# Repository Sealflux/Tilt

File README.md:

## Tilt
-- I put photo here once I have!

## Description
A motion-controlled keychain game console. Built around the Seeed XIAO ESP32C3 with an SSD1306 OLED and MPU6050 accelerometer. Planning to make a ball tilt game maybe

## Features
- Its a game console with an accelerometer in it!
- Play cool game or design one yourself!
- Put it on your backpack as its supposed to be a keychain thingabob
- Rechargeable Battery!
## Hardware
- Seeed Xiao ESP32-C3
- SSD1306 128x64 OLED (I2C)
- Tactile Push Button
- 3D accelerometer and 3D magnetometer
- Buzzer
- Mystery LiPo Battery(Haven't decided which one on amazon yet)
- 3D-printed case

## Bill of Materials (BOM)

| Qty | Part Name | Designator | Costs | Link/LCSC Number |
|:---:|-----------|:----------:|:-----:|-------------|
| 1 | Seeed XIAO ESP32-C3 | U2 | $6.35 | [Link](https://wiki.seeedstudio.com/XIAO_ESP32C3_Getting_Started/) |
| 1 | LiPo Battery | BT1 | | I'll find one on amazon eventually |
| 1 | 0.96" OLED Display | U3 | $2.24 | [C5248080](https://www.lcsc.com/product-detail/C5248080.html) |
| 1 | Tactile Button | SW1 | $0.56 | [C2913653](https://www.lcsc.com/product-detail/C2888493.html) |
| 1 | Accelerometer | U1 | $4.04 | [C2913653](https://www.lcsc.com/product-detail/C2913653.html) |
| 1 | Capacitor – 220 nF | C3 | $0.96 | [C412252](https://www.lcsc.com/product-detail/C412252.html) |
| 2 | Ceramic Capacitor – 100 nF | C1,C2 | $0.88 | [C60474](https://www.lcsc.com/product-detail/C60474.html) |
| 1 | Aluminum Capacitor – 10 µF | C4 | $0.74 | [C192100](https://www.lcsc.com/product-detail/C192100.html) |
| 1 | Buzzer | BUZZER1 | $0.32 | [C49246964](https://www.lcsc.com/product-detail/C49246964.html) |
| 1 | 3D Printed Case | N/A | Idk whatever fliament you use makes costs dependent | N/A |
| 1 | Shipping | $52.39 | $6.20(Seeed) + $11.33(LCSC) + $6.99(Amazon) + $27.87(JLCPCB) | N/A |

## Steps To Reproduce
1. Order the PCB from whatever PCB manufacturer you like, download gerbers.zip from Production folder
2. 3D print the case, Its in the production folder. Use whatever filament you want, probably PLA.
3. Order the parts using the BOM ^^^
4. Solder the parts onto the PCB
5. Connect the LiPo battery to the PCB
6. Flash your firmware/game onto it!
7. Assemble case, sand the surfaces of top and bottom and then superglue or idk use tape. I didn't add screws for some reason.
8. Press the button and play the game!
## Firmware
this is hardware!
## Schematic

## PCB

## PCBA

## Case

## Side View Below

## Demo(Idk probably after horizons event)

Link: (TBD After I finish hardware)

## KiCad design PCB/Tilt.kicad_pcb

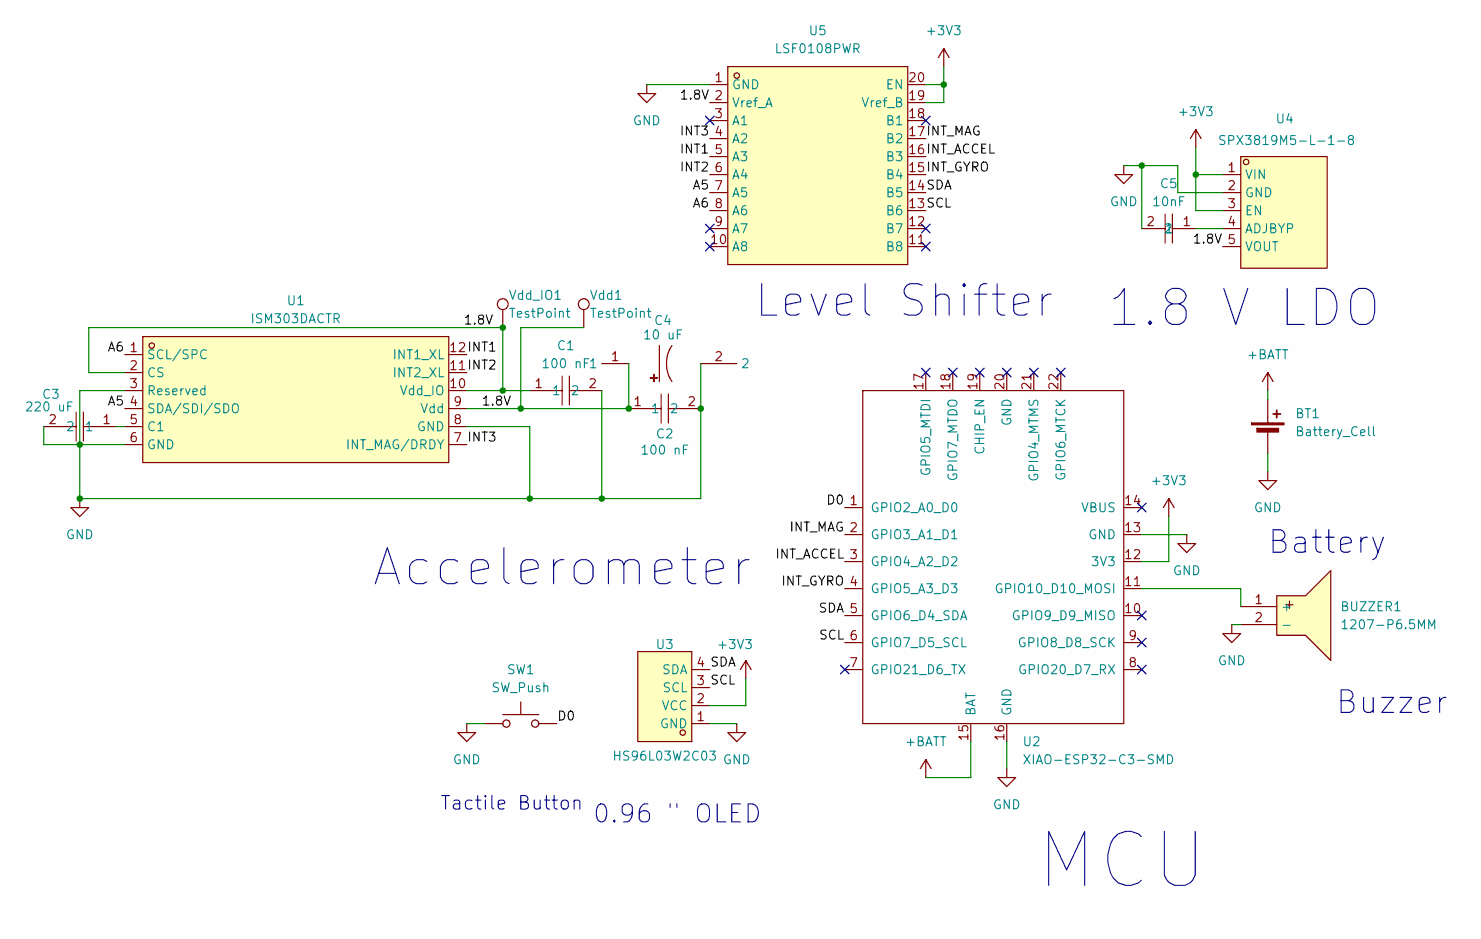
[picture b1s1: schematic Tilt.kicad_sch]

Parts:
BT1: Battery_Cell; PinHeader_1x02_P2.54mm_Vertical
BUZZER1: 1207-P6.5MM; BUZ-TH_BD12.5-P6.50-D1.4; MPN 1207-P6.5MM; LCSC Part C49246964
C1, C2: 100 nF; C0402; MPN CC0402KRX7R7BB104; LCSC Part C60474
C3: 220 uF; C1206; MPN GRM31CR60J227ME11L; LCSC Part C412252
C4: 10 uF; CAP-TH_BD5.0-P2.00-D0.8-FD; MPN ECR1HBK100MLL050011; LCSC Part C192100
C5: 10nF; C0603; MPN CC0603KRX7R9BB103; LCSC Part C100042
SW1: SW_Push; SW-TH_4P-L4.5-W4.5-P3.00-LS4.8
U1: ISM303DACTR; VLGA-12_L2.0-W2.0-P0.50-BL; MPN ISM303DACTR; LCSC Part C2913653
U2: XIAO-ESP32-C3-SMD; XIAO-ESP32-C3-DIP-SMD
U3: HS96L03W2C03; OLED-TH_L27.8-W27.2-P2.54_C9900033791; MPN HS96L03W2C03; LCSC Part C5248080
U4: SPX3819M5-L-1-8; SOT-23-5_L3.0-W1.7-P0.95-LS2.8-TL; MPN SPX3819M5-L-1-8/TR; LCSC Part C24639
U5: LSF0108PWR; TSSOP-20_L6.5-W4.4-P0.65-LS6.4-BL; MPN LSF0108PWR; LCSC Part C190219
Vdd1: TestPoint; TestPoint_Pad_D2.5mm
Vdd_IO1: TestPoint; TestPoint_Pad_D2.5mm

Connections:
+3V3: U2.12 (3V3), U3.2 (VCC), U4.1 (VIN), U4.3 (EN), U5.19 (Vref_B), U5.20 (EN)
+BATT: BT1.1 (+), U2.15 (BAT)
/1.8V: C1.1, C2.1, C4.1, U1.2 (CS), U1.9 (Vdd), U1.10 (Vdd_IO), U4.5 (VOUT), U5.2 (Vref_A), Vdd1.1 (1_1), Vdd_IO1.1 (1_1)
/A5: U1.4 (SDA/SDI/SDO), U5.7 (A5)
/A6: U1.1 (SCL/SPC), U5.8 (A6)
/D0: SW1.2, U2.1 (GPIO2_A0_D0)
/INT1: U1.12 (INT1_XL), U5.5 (A3)
/INT2: U1.11 (INT2_XL), U5.6 (A4)
/INT3: U1.7 (INT_MAG/DRDY), U5.4 (A2)
/INT_ACCEL: U2.3 (GPIO4_A2_D2), U5.16 (B3)
/INT_GYRO: U2.4 (GPIO5_A3_D3), U5.15 (B4)
/INT_MAG: U2.2 (GPIO3_A1_D1), U5.17 (B2)
/SCL: U2.6 (GPIO7_D5_SCL), U3.3 (SCL), U5.13 (B6)
/SDA: U2.5 (GPIO6_D4_SDA), U3.4 (SDA), U5.14 (B5)
GND: BT1.2 (-), BUZZER1.2 (-), C1.2, C2.2, C3.2, C4.2, C5.2, SW1.1, U1.3 (Reserved), U1.6 (GND), U1.8 (GND), U2.13 (GND), U2.16 (GND), U3.1 (GND), U4.2 (GND), U5.1 (GND)
unnamed: BUZZER1.1 (+), U2.11 (GPIO10_D10_MOSI)
unnamed: C3.1, U1.5 (C1)
unnamed: C5.1, U4.4 (ADJBYP)

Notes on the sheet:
Tactile Button
1.8 V LDO
Buzzer
MCU
Accelerometer
Level Shifter
0.96 " OLED
Battery

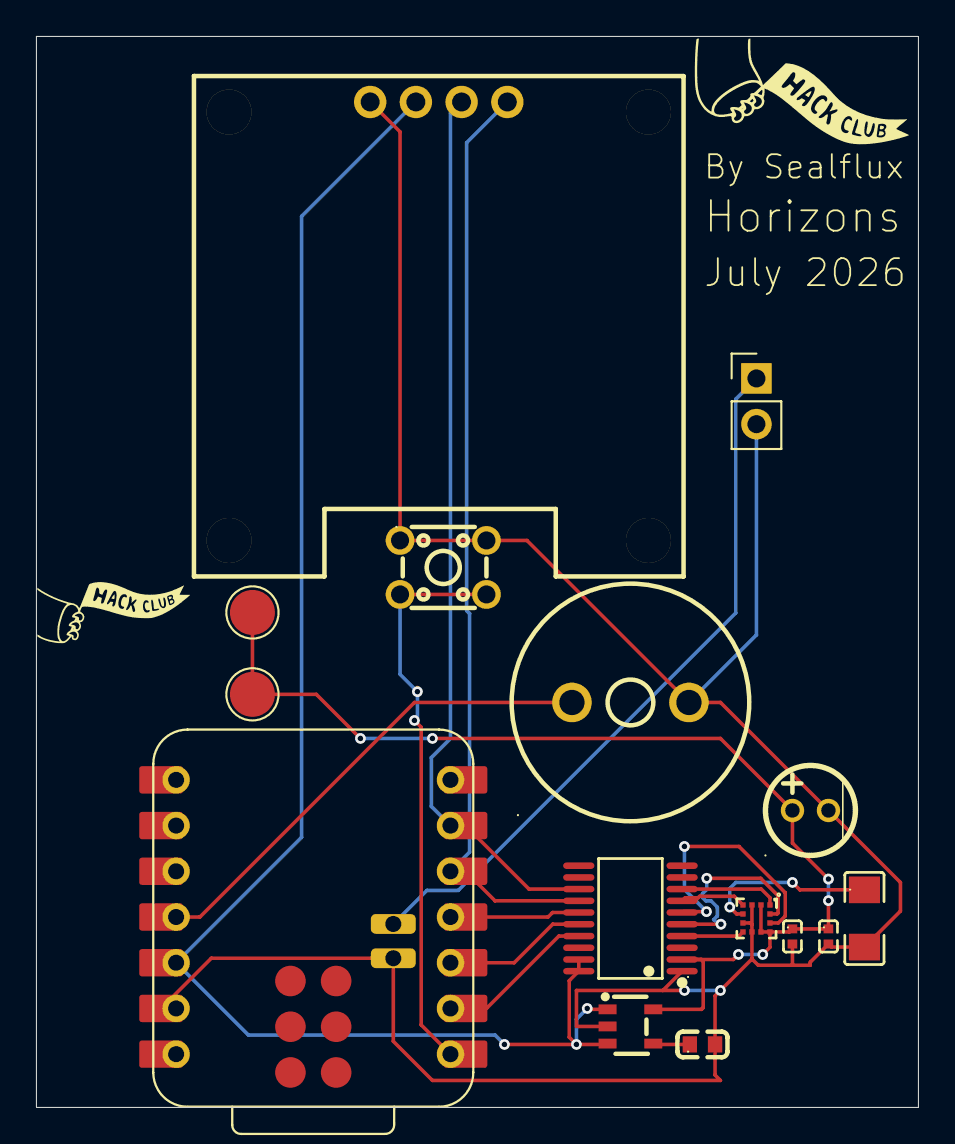
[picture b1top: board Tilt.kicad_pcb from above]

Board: 2 copper layers, 49.0 x 59.5 mm, 15 parts (0 on the bottom side), 18 nets.
